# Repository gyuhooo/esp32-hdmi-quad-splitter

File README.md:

# esp32-hdmi-quad-splitter

Full HD のテスト映像を **1 台のデバイス内で生成し、HDMI 4 本に出力する**装置の設計。

> リポジトリ名は初期案(ESP32 + 分配器)に由来します。現在の方針は **FPGA によるテストパターン発生器**です。
> mp4 の再生は行わず、カラーバー・フレームカウンタ・タイムコードをロジックで生成して 4 本を独立したタイミングで出します。

## 現在の方針: FPGA 4 出力テストパターン発生器

| 項目 | 内容 |
|---|---|
| FPGA | Xilinx Artix-7 XC7A35T 以上(無償 Vivado、MMCM ×4 で 6 種のピクセルクロックを 1 ppm 以内で生成) |
| HDMI 送信 | ADI ADV7513 ×4(24bit RGB パラレル入力 → HDMI 1.4、1080p60 対応、資料公開) |
| 出力 | 1080p / 720p / 480p × 29.97p / 59.94p / 30p / 60p を出力ごとに独立して設定 |
| 画面 | 75% カラーバー、動くボックス(コマ落ち検出)、グレースケール、外枠、ラベル、6 桁フレームカウンタ、タイムコード |
| 状態 | HDL 一式と iverilog シミュレーション済み。基板は 2 枚(FPGA メイン基板 115 × 72 mm + HDMI キャリア基板 115 × 38 mm、どちらも 6 層)で、回路図・レイアウト・ガーバーまで生成済み。実機は未評価 |

```
100 MHz --> [Artix-7: MMCM x4 -> timing -> pattern] --24bit RGB--> [ADV7513] --> HDMI OUT1
                                   |                              [ADV7513] --> HDMI OUT2
                                   |                              [ADV7513] --> HDMI OUT3
                                   +---------- I2C 初期化 ------->[ADV7513] --> HDMI OUT4
```

シミュレーション結果(1080p 59.94 / 480p 59.94):

詳細は [docs/fpga-pattern-generator.md](docs/fpga-pattern-generator.md)。

### 試す

```
cd sim && make MODE=1 FRAME=2     # iverilog で 1080p59.94 の 1 フレームを frame.ppm に保存
```

### 基板(hardware/)

2 枚構成。下が FPGA メイン基板(XC7A35T-1FTG256C、QSPI フラッシュ、JTAG、100 MHz、USB-C 5 V → 1.0 / 1.8 / 3.3 V)、
上が HDMI キャリア基板(ADV7513 ×4、TPD12S016 ×4、HDMI ×4、USB-C 5 V 入力、3.3 V バック、1.8 V LDO ×4)で、2×40 ソケット 2 個で重ねる。
[hardware/README.md](hardware/README.md)(キャリア基板)と [hardware/fpga_main/README.md](hardware/fpga_main/README.md)(メイン基板)に構成・検証状況・発注前チェックリストがある。
FPGA のピン割り当ては生成済みで、`constraints/board.xdc` がそのまま Vivado で使える。

FPGA メイン基板(6 層、115 × 72 mm、表面。上部 y < 38 mm にキャリア基板が重なる):

簡易 3D(`hardware/fpga_main/3d/viewer.html`):

基板の簡易 3D モデル(`hardware/quad_hdmi_tx/3d/`、three.js ビューア付き):

基板レイアウト(6 層、115 × 38 mm、表面):

### ディレクトリ

| パス | 内容 |
|---|---|
| hardware/ | KiCad 7 プロジェクト ×2(FPGA メイン基板、HDMI キャリア基板)、BOM、ピン割り当て表、生成スクリプト |
| hdl/ | Verilog ソース(タイミング、パターン、文字重畳、MMCM、ADV7513 初期化、トップ) |
| sim/ | iverilog テストベンチと Makefile |
| constraints/ | Vivado 制約ファイルの例 |
| tools/make-font.py | フォント ROM 生成 |
| docs/ | 設計文書 |

## 検討経緯

| 案 | 判定 | 理由 |
|---|---|---|
| ESP32 + LT86104SX 分配器 | 不採用 | ESP32 は映像を生成できない。分配器は同一映像しか出せない |
| RK3588 で mp4 を再生し 4 CRTC へ | 代替案 | 自己完結するが、Linux と SoM が要り、出力ごとの独立タイミングは難しい。[docs/self-contained.md](docs/self-contained.md) |
| Ambarella A7 | 不採用 | HDMI 1 本、SDK は NDA |
| **FPGA パターン発生器** | **採用** | テストパターンで十分。出力ごとに独立したクロックを持て、BOM が小さい |

---

## 初期案(参考): ESP32 + LT86104SX 分配器

以下は「外部 HDMI ソース + 分配器を ESP32 で制御する」初期案の記録です。同一映像の 4 分配だけが目的ならこの構成でも成立します。

### 結論: 実現可能(ただし ESP32 は「制御担当」)

| 役割 | 担当 | 備考 |
|---|---|---|
| Full HD 映像の生成 | PC(ffmpeg) | [docs/video-source.md](docs/video-source.md) |
| Full HD 映像の再生(HDMI ソース) | **Raspberry Pi 4/5 など**(mpv) | ESP32 単体では不可 |
| 1→4 分配、HDCP リピータ、EDID 処理 | LT86104SX | 1080p60 まで、3.4 Gbps/ch |
| IC の初期化・EDID 管理・入力監視・出力 ON/OFF | ESP32(I2C マスタ) | Wi-Fi 経由でリモート制御も可 |

- LT86104SX は入力 HDMI 信号をそのまま 4 系統へ複製する IC で、映像の生成や解像度変換は行いません。
- ESP32(無印 / S3 / C3)には TMDS 出力が無く、1080p60(約 4.5 Gbps)の映像を生成する帯域も持たないため、**映像ソースにはなれません**。
- したがって「ESP32 + LT86104SX」で成立するのは **`HDMI ソース → LT86104SX → HDMI×4` を ESP32 が I2C で制御する構成** です。同じ映像を 4 台のモニタに出す用途なら、これで十分です。

### 4 本が「別々の映像」である必要がある場合

スプリッタでは実現できません。RK3588(4 画面同時出力)や 4 出力 GPU(ASUS GT710-4H など)を使ってください。

### ESP32-P4 を映像ソースにできるか

ESP32-P4 は MIPI-DSI(2 レーン)と H.264 デコーダを持つため、`ESP32-P4 → LT9611 / LT8912B (DSI→HDMI) → LT86104SX` で **1080p30 程度のテストパターン/静止画** を出すことは原理的に可能です。ただし 1080p60(RGB888 で約 3.56 Gbps)は DSI 帯域を超えるため、59.94p / 60p のテストは不可です。本リポジトリでは扱いません。

### ブロック図

```
[PC: ffmpeg で生成] --master.mp4--> [Raspberry Pi: mpv でループ再生]
                                              | HDMI 1080p
                                        [LT86104SX] --HDMI--> OUT1
                                           |   |------HDMI--> OUT2
                                           |   |------HDMI--> OUT3
                                           |   '------HDMI--> OUT4
                                           | I2C (SDA/SCL), RESET, INT
                                        [ESP32] <--Wi-Fi--> OBS-RemoteControl 等
```

### 最小構成の BOM

### 映像ソース

| 部品 | 数 | 備考 |
|---|---|---|
| Raspberry Pi 4(2 GB 以上)または Pi 5 | 1 | mpv でループ再生 |
| microSD 16 GB 以上 | 1 | Raspberry Pi OS Lite 64bit |
| micro HDMI → HDMI ケーブル | 1 | LT86104SX 入力へ |
| 5V 3A(Pi4)/ 5V 5A(Pi5)電源 | 1 | |
| 生成用 PC(ffmpeg) | 1 | 手元の PC で可 |

### スプリッタ + 制御

| 部品 | 数 | 備考 |
|---|---|---|
| LT86104SX(LQFP-128) | 1 | Lontium。データシート/レジスタ仕様は代理店経由(NDA)で入手 |
| ESP32 モジュール(ESP32-WROOM-32 / S3) | 1 | I2C マスタ、Wi-Fi |
| HDMI レセプタクル | 5 | 入力 1、出力 4 |
| 3.3V / コア用レギュレータ | 各 1 | 電圧は LT86104SX データシートで要確認 |
| ESD 保護ダイオード(TMDS 用) | 5 セット | 入出力各ポート |
| 水晶(周波数はデータシートで要確認) | 1 | |
| I2C プルアップ 4.7 kΩ | 2 | |
| 5V → HDMI +5V(各出力) | 4 | 出力側ホットプラグ用に 5V を給電 |

完成品の 1×4 スプリッタ基板(LT86104 搭載)を購入し、基板上の I2C を ESP32 に引き出す方法が最も安価で確実です。

### 使い方(映像の生成と再生)

```
# PC で生成 (ffmpeg 必須)
tools/generate-test-video.sh out/test-video 3

# Raspberry Pi に master.mp4 をコピーしてループ再生 (mpv 必須)
tools/play-loop.sh master.mp4
# セグメントごとに HDMI 出力モードを切替してテストする場合
tools/play-loop.sh --native segments
```

### 詳細

- [docs/self-contained.md](docs/self-contained.md): **現在の方針**。デバイス内で生成して 4 本出す構成
- [docs/video-source.md](docs/video-source.md): 映像の生成と再生機に必要なもの(初期案)
- [docs/feasibility.md](docs/feasibility.md): 可否判断の根拠、帯域計算
- [docs/hardware.md](docs/hardware.md): 配線、電源、注意点
- [docs/i2c-control.md](docs/i2c-control.md): ESP32 からの制御シーケンス
- [tools/](tools/): テスト映像の生成・再生スクリプト
- [firmware/](firmware/): ESP-IDF 用 I2C 制御の雛形

### 関連

- [OBS-RemoteControl](https://github.com/gyuhooo/OBS-RemoteControl)(テスト映像スクリプトの元)
- [LT86104SXE Product Brief (Lontium)](https://www.lontiumsemi.com/UploadFiles/2021-03/LT86104SXE_brief_R1.pdf)

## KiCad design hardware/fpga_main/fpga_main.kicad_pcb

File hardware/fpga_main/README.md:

# FPGA メイン基板 (XC7A35T-1FTG256C)

キャリア基板 `quad_hdmi_tx`(rev B、ADV7513 ×4 → HDMI ×4)をソケットで上に重ねて使う、FPGA 搭載のメイン基板。
2 枚構成の下側で、電源・コンフィグ用フラッシュ・JTAG・100 MHz 発振器・ユーザ I/O を持つ。
キャリア基板の裏面ヘッダ J7/J8(2×40 SMD)に、この基板の表面ソケット J1/J2(2×40 THT)が嵌合する。

| ファイル | 内容 |
|---|---|
| fpga_main.kicad_pro / *.kicad_sch | KiCad 7 プロジェクト(ルート + 電源 + FPGA I/O + FPGA コンフィグ/電源ピン + キャリアソケット + ユーザ I/O) |
| fpga_main.pdf | 回路図 PDF(6 ページ) |
| netlist.net | kicad-cli で書き出したネットリスト |
| bom.csv, bom_grouped.csv | 部品表(リファレンス別 / 集計、MPN 付き) |
| fpga_pinmap.csv | 全 256 ボールの表: ピン名、バンク、ネット、キャリアのヘッダピン、方向、エスケープ層。`gen/gen_xdc.py` が `constraints/board.xdc` を作る元 |
| roles.json | 自動採番された R/C の役割 → リファレンス(レイアウト生成が配置に使う) |
| fpga_main.kicad_pcb | 基板レイアウト rev A(6 層、115 × 72 mm)。`gen/gen_fpga_pcb.py` が配置・プレーン・BGA ファンアウトを生成し、FreeRouting で自動配線 |
| drc.rpt / drc_pre.rpt | DRC レポート(配線後 / 配線前) |
| fab/ | ガーバー、ドリル、CPL、各層の PDF(`gen/export_fab.sh fpga_main`) |
| 3d/ | STEP(基板のみ)、簡易 3D モデル(OBJ + テクスチャ)、three.js ビューア |

## 回路構成

```
USB-C 5V ─ F1(PTC 2A) ─ +5V ─┬─ U3 AP63200 ─ +1V0 (VCCINT/VCCBRAM)   EN: 即時
                             ├─ U4 AP63200 ─ +1V8 (VCCAUX)           EN: 100k + 1uF  (約 30 ms 遅れ)
                             └─ U5 AP63203 ─ +3V3 (VCCO 全バンク, フラッシュ, 発振器, LED) EN: 100k + 2.2uF (約 60 ms 遅れ)
U1 XC7A35T-1FTG256C ─┬─ U2 W25Q32JV (QSPI x4、Master SPI、M[2:0]=001)
                     ├─ J3 JTAG 2x7 2.0 mm (Xilinx 14 ピン) / J4 JTAG 1x6 (Digilent HS2 配列) ─ 並列
                     ├─ X1 100 MHz → D4 (IO_L12P_T1_MRCC_35)
                     ├─ SW1 PROG(PROGRAM_B)、SW2 RST(RST_N)、SW3 DIP ×4、D1-D7 LED(PWR/DONE/INIT/USER0-3)、J5 PMOD(8 I/O)
                     └─ J1/J2 2x40 ソケット ─ キャリア基板 J7/J8 (124 信号 + GND 34 + FPGA_5V 2)
```

### FPGA まわり

| 要素 | 内容 | 根拠・備考 |
|---|---|---|
| XC7A35T-1FTG256C | 170 I/O(バンク 14/15/34/35、各 50/50/20/50)、VCCO は全バンク 3.3 V | FTG256 は 1.0 mm ピッチの 16×16 BGA。6 層で全ピンを引き出せる(下記エスケープ) |
| VCCINT / VCCBRAM = 1.0 V | 同じレール(-1 スピードグレードでは VCCBRAM = VCCINT = 1.0 V が可) | DS181 |
| VCCAUX / VCCADC / VCCBATT = 1.8 V | XADC は未使用: VREFP/VREFN/VP/VN/GNDADC → GND、DXP/DXN 開放 | UG480 / UG475 |
| コンフィグ | Master SPI x4。M0 = 4.7k プルアップ、M1/M2 = GND、CFGBVS = VCCO_0 = 3.3 V | UG470 |
| PROGRAM_B | 4.7k プルアップ + タクトスイッチ SW1 | |
| INIT_B | 4.7k プルアップ + 赤 LED(Low のとき点灯 = 未コンフィグ / CRC エラー) | |
| DONE | 330 Ω プルアップ + 緑 LED(1k) | UG470 の推奨 330 Ω。LED 点灯時も DONE は約 3.0 V で High |
| フラッシュ | W25Q32JVSSIQ(32 Mbit、ビットストリーム 17.5 Mbit) CS/WP/HOLD 4.7k プルアップ、CCLK は E8、D0-D3 は J13/J14/K15/K16、FCS_B は L12 | バンク 14 のコンフィグ兼用ピン |
| JTAG | TMS/TDI 4.7k プルアップ(TCK/TDO は内蔵プルアップのみ) | |
| 発振器 | ASEM1-100.000MHZ-LC-T(3.2 × 2.5 mm、3.3 V、±50 ppm)、MRCC ピン D4 へ | hdl/top.v の clk100 |
| デカップリング | +1V0: 100 µF + 4.7 µF ×2 + 0.47 µF ×4、+1V8: 47 µF + 4.7 µF + 0.47 µF ×2、+3V3: 47 µF + 4.7 µF ×4(バンクごと) + 0.47 µF ×9 | UG483 の FTG256 推奨数量以上。0.47 µF は BGA 直下の十字通路と周囲(裏面) |

### キャリア基板とのインタフェース

- J1(= キャリア J7)、J2(= キャリア J8): 2×40 メス(Sullins PPTC402LFBN-RC、高さ 8.5 mm)。ピン n はキャリアの同じ番号のピンと一致する。
- 位置はキャリアの J7/J8 のピン位置の鏡像: J1 の奇数ピン y = 16.93 / 偶数 19.47 mm、J2 の奇数 32.33 / 偶数 34.87 mm、列 k の x = 2.07 + 2.54 (k−1) mm(基板左上が原点、両基板とも同じ原点・同じ向き)。
- キャリアの SMD ヘッダの本体(2.54 mm)+ ソケット(8.5 mm)で基板間は約 11 mm。取付穴 H1-H4 はキャリアと同じ位置(26.2, 3)(51.6, 3)(77, 3)(112, 35)で、M3 × 11 mm のスペーサで固定する。
- y < 38 mm はキャリアの真下で、ソケット以外の部品は置いていない(キャリア裏面の LDO・コンデンサと干渉しない)。
- FPGA_5V(J2 の 39/40 ピン)は JP1 で +5V に繋げる。既定は開放(両基板とも自分の USB-C から給電)。両基板の JP1 を閉じると片方の USB-C で両方を動かせる(合計 2 A まで)。
- I2C のプルアップ(4.7 kΩ)はキャリア側にある。

### ユーザ I/O

| 部品 | ネット | FPGA ボール | 用途 |
|---|---|---|---|
| D4-D7(緑) | LED0-3 | R10, R11, T12, R12 | hdl/top.v の `led[3:0]`(各チャネルの初期化完了) |
| SW2 | RST_N(10k プルアップ、0.1 µF) | T3 | `rst_n` |
| SW3 DIP ×4 | SW0-3(閉で Low、内蔵プルアップを XDC で有効化) | T13, R13, T14, T15 | 予備(ビデオモード切替用) |
| J5 PMOD 2×6 | PMOD_1-4 / 7-10、GND、3.3 V | E5, E6, F5, G5, H5, J5, K5, L5(バンク 35) | 予備 I/O(Digilent Pmod 配列) |
| D1-D3 | 3.3 V / DONE / INIT_B | — | 電源 / コンフィグ完了 / 未コンフィグ |

## ピン割り当て

`gen/fpga_common.py` が決める(回路図とレイアウトの両方が同じモジュールを使うので食い違わない)。

1. **BGA エスケープ計画**: ボールのリングごとに引き出し方を固定する。リング 1(最外周)は表面パッドから直接、リング 2 は表面でリング 1 のパッドの隙間へ、
   リング 3-4 は外向き対角のセルに dog-bone ビアを打ち In2(SIG1)で整数格子線に沿って外へ、リング 5 以降の信号(JTAG、CCLK、DONE、INIT_B、PROGRAM_B、M0、PMOD)は In3(SIG2)。
   整数格子線は層ごとに 1 本の配線が占有し、各ビアは隣接 4 格子点のどれかから最寄りの辺へ向かう(占有点が重ならないよう貪欲に割り当て)。GND/電源ボールは dog-bone ビアでプレーンへ。
2. **ヘッダ信号の割り当て**: 124 本のヘッダ信号を x 順(列 k、列内は J1 奇 / J2 奇 / J2 偶 / J1 偶)に並べ、BGA の出口を周回順(左下 → 左辺 → 上辺 → 右辺 → 右下)に並べたものへ単調に対応させる。
   124 個の連続した出口の窓のうち、ヘッダピンまでの距離の総和が最小のものを選ぶ。交差が出ないので、ソケットまでの配線が素直になる。
3. 用途が決まっているボール(フラッシュ、クロック、LED、スイッチ、PMOD)は先に確保する。

結果(`fpga_pinmap.csv`): OUT1 = バンク 34/35(左辺・下辺左)、OUT2 = バンク 35(上辺左・左辺)、OUT3 = バンク 15(上辺右)、OUT4 = バンク 14/15(右辺・下辺右)。
I2C_A は H4/H2(バンク 35)、I2C_B は E15/E16(バンク 15)。未使用 I/O はリング 1-4 に 10 本、リング 5-6 に 11 本(開放)。

Vivado 用の制約は `python3 hardware/gen/gen_xdc.py > constraints/board.xdc`(hdl/top.v のポート名、`SLEW FAST`、CFGBVS/CONFIG_VOLTAGE、QSPI x4、非同期クロックグループ)。

## 基板レイアウト

### 配置(rev A: 115 × 72 mm)

```
y=0  ┌──────────────────────────────────────────────────────────────────────┐
     │  (キャリア基板の真下: H1 H2 H4 取付穴、部品なし)                       │
 17  │  J1 ████████████████████████████████████████████ (2x40 ソケット)       │
 33  │  J2 ████████████████████████████████████████████                     H3 │
 38  ├─ キャリア基板の下端 ─────────────────────────────────────────────────┤
     │ PMOD                      ┌─────────┐      U2 flash  C(3V3 47u) USB-C │
 55  │ J5   X1 100MHz  caps      │ U1 BGA  │ caps  R pull-up  U3   U4   U5   │
     │                           │ 16x16   │      1V0  1V8  3V3 bucks         │
 69  │ H5 J3 JTAG2mm  J4 JTAG1x6  PROG RST  DIP  LEDs x7           H6        │
 72  └──────────────────────────────────────────────────────────────────────┘
```

- FPGA は露出部の中央 (51.6, 55):ヘッダ中心 x と同じで、左右の信号本数が揃う。ソケット J2 の下端(y 35.7)から BGA のエスケープ終端(y 46)まで 10 mm の帯で 124 本をファンアウトする。
- J1 の信号は J2 のスルーホール列を内層で抜ける。ソケットのパッドはライブラリの 1.7 mm から 1.5 mm(穴 1.0 mm、アニュラ 0.25 mm)に縮めて列の隙間を 1.04 mm にし、隙間 1 つに 0.15 mm 配線 2 本(4 層で最大 8 本)が通る。
- フラッシュ U2 は BGA 右(バンク 14 のコンフィグピンは右辺の行 8-10 から出る)、発振器 X1 は左(D4 は In2 で左辺へ)。
- 電源は右下: USB-C は右辺、バック 3 個を横並び(1.0 V が FPGA に最も近い)。+5V は In4 の櫛形プレーン(バー + 各バックの IN 側の歯)。
- +1V0 は In4 の島(BGA 中央、VCCINT/VCCBRAM のビアを含み VCCO_0 のビアは避ける)→ 列 7.5 の通路(ビアのない中央の十字)→ 下の帯(y 65-67.6)→ U3 出力。
- +1V8 は裏面ベタ: BGA 中央右(VCCAUX ×4、VCCADC、VCCBATT)→ 行 7.5 の通路 → U4 出力への帯。
- デカップリングは裏面。0.47 µF は BGA 直下の十字通路(列 7.5 に +1V0 ×3、行 7.5 に +1V0 ×1 と +1V8 ×2、ビアはセル中心 = 半整数格子)と BGA の左右(VCCO)。バルクは下の帯と各バックの脇。

### 層構成(6 層、1.6 mm)

| 層 | 用途 |
|---|---|
| F.Cu | 部品、BGA リング 1-2 のエスケープ、配線後に GND ベタ |
| In1.Cu | GND プレーン |
| In2.Cu (SIG1) | BGA リング 3-4 のエスケープ(整数格子線)、信号 |
| In3.Cu (SIG2) | 深いリングの信号のエスケープ、信号 |
| In4.Cu (PWR) | +3V3 プレーン + +1V0 の島/腕/帯 + +5V の櫛 |
| B.Cu | デカップリング、+1V8 ベタ(BGA 中央右)、信号、配線後に GND ベタ |

### ルール

配線 0.15 mm / クリアランス 0.15 mm(BGA の 1.0 mm ピッチで、ビア 0.5 mm の隙間 0.5 mm に 0.15 mm 配線を 1 本通すため)、ビア 0.5 / 0.3 mm(アニュラ 0.1 mm)、
穴-銅 0.18 mm、銅-外形 0.3 mm。電源ネットクラス(+5V/+3V3/+1V0/+1V8/VBUS/FPGA_5V/SW ノード)は 0.4 mm 幅、ビア 0.6 mm。
dog-bone ビアは隣のボールパッド(0.4 mm)から 0.26 mm、整数格子線の配線はビアパッドから 0.175 mm 離れる。

### 生成と配線のパイプライン

```sh
cd hardware/gen
./build_fpga_main.sh                      # 回路図 → netlist.net → 基板 (配置 + BGA ファンアウト + 電源ビア) → ゾーン塗り + drc_pre.rpt
PCB_PROJECT=fpga_main python3 route_pcb.py export        # fpga_main.dsn
(cd ../fpga_main && xvfb-run -a -s "-screen 0 1280x1024x24" java -jar freerouting-1.9.0.jar -de fpga_main.dsn -do fpga_main.ses -mp 24 -oit 1.0)
PCB_PROJECT=fpga_main python3 route_pcb.py import        # SES 取り込み、未接続の島の接続、外層 GND ベタ、drc.rpt
PCB_PROJECT=fpga_main python3 layout_report.py
./export_fab.sh fpga_main                 # fab/
PY=../../../scratch/venv/bin/python ./make_3d.sh fpga_main   # 3d/: STEP、簡易 OBJ、テクスチャ、viewer.html (PY は Pillow/numpy 入りの python)
PCB_PROJECT=fpga_main ../../scratch/venv/bin/python render_images.py   # docs/images/fpga-main-*.png
python3 gen_xdc.py > ../../constraints/board.xdc
python3 check_fpga_netlist.py ../fpga_main/netlist.net && python3 check_stack.py
```

## 検証状況

- 回路図: `gen/check_fpga_netlist.py` でネットリストを検査(ヘッダ信号 124 本が J1/J2 と U1 の 2 ノード、全 256 ボールが接続または NC、電源ネットに信号ボールが混ざっていない、孤立ネットなし)。ERC は未実施(kicad-cli 7 に無い)。
- 2 枚構成: `gen/check_stack.py` でキャリアのヘッダピンとソケットピンの位置(誤差 0.000 mm)、ピンごとのネット、取付穴 H1-H4 の一致を確認。
- レイアウト: 配線前 DRC はクリアランス / 穴 / コートヤード違反 0(BGA ファンアウト 149 ビア + 112 エスケープ、電源ファンアウトビア 125)。配線後の結果は下記(未接続 0、違反 0)。
- 実機・Vivado での実装は未実施。

### レイアウトの結果

| 項目 | 値 |
|---|---|
| 配線 / ビア | 2155 本 / 405 個(スクリプトの固定配線 522 本・ビア 285 個を含む。ビアは 0.5/0.3 mm ×279、0.6/0.3 mm ×126) |
| DRC(pcbnew API) | 未接続 0、クリアランス / 穴 / 外形 / コートヤード / シルク違反 0。残り 109 件は `lib_footprint_issues`(ライブラリ名なしで読み込んだフットプリントの照合情報)のみ |
| ヘッダ信号 124 本の配線長 | OUT1 33〜83 mm(平均 56)、OUT2 14〜49(30)、OUT3 13〜46(28)、OUT4 31〜89(55)。FR4 の 90 mm は約 0.6 ns で、148.5 MHz SDR の余裕(数 ns)に収まる |
| 層別の配線長 | F 1077 mm、In2 (SIG1) 4072、In3 (SIG2) 1039、B 412 |
| 自動配線 | FreeRouting 1.9.0、40 パス、約 8 分(ルータにはビア禁止領域: BGA 直下・+1V0 の腕・裏面の +1V8 帯・外形から 0.45 mm を渡す)。INIT_B の LED 側 1 区間だけ `route_pcb.py` の MANUAL で手配線 |

| 層 | 画像 |
|---|---|
| 表面 (F.Cu) |  |
| 裏面 (B.Cu、ミラー表示) |  |
| 内層 1 (GND) |  |
| 内層 2 (SIG1: BGA リング 3-4 のエスケープ) |  |
| 内層 3 (SIG2) |  |
| 内層 4 (PWR: +3V3 / +1V0 島 / +5V 櫛) |  |

### 3D モデル

`3d/`: STEP(基板のみ)、簡易 OBJ(部品は寸法表の直方体)、three.js ビューア `3d/viewer.html`(ブラウザで開く。ドラッグで回転)。
部品の外形は近似なので、正確な 3D が要るときは KiCad の 3D ライブラリを入れて `kicad-cli pcb export step` を再実行する。

| 斜め | 表 | 裏 |
|---|---|---|
|  |  |  |

## 発注前チェックリスト

- [ ] ソケット J1/J2 の高さ(8.5 mm)とキャリア側ヘッダの嵌合長(Samtec TSM の 0.230" ピン)を実物で確認。別の高さのソケットならスペーサ長を合わせる。
- [ ] UG483 の表(FTG256 の必要コンデンサ数)と `fpga_cfg.kicad_sch` のデカップリング数量を照合(ここでは余裕を持って多めにしている)。
- [ ] AP63200 の FB 分圧(1.0 V: 10k / 40.2k、1.8 V: 24.9k / 20k)と EN の RC 遅延(データシートの EN しきい値 1.2 V 前後)を確認。
- [ ] JTAG ヘッダの配列(J3: Xilinx 14 ピン 2 mm、J4: Digilent HS2 6 ピン)を使うケーブルと照合。
- [ ] DIP スイッチ(Copal CHS-04B)、タクトスイッチ(C&K KMR2)、発振器(Abracon ASEM1)の入手性。代替品はフットプリントを合わせる。
- [ ] フラッシュ W25Q32JV: Vivado のメモリ構成ファイルは `w25q32jv-spi-x1_x2_x4`。
- [ ] 1.0 mm ピッチ BGA の 0.15 / 0.15 mm ルール、ビア 0.3 / 0.5 mm(アニュラ 0.1 mm)が製造業者の 6 層仕様に収まるか。JLCPCB の 6 層は配線/間隔 0.09 mm、ビア穴 0.2 mm(径 0.35 mm 程度)以上、PTH のアニュラ 0.13 mm なので余裕があるが、注文時の仕様ページで再確認する。
- [ ] BGA 直下の In1/In4 プレーンはビアの間の 0.2 mm 幅のメッシュになる(1.0 mm ピッチ、ビア 0.5 mm + クリアランス 0.15 mm)。通常の設計と同じだが、ガーバーで確認。
- [ ] 外層 GND ベタは BGA 直下にも入る(パッド間 0.3 mm)。不要なら `route_pcb.py` の finish 段で BGA 領域を除外する。

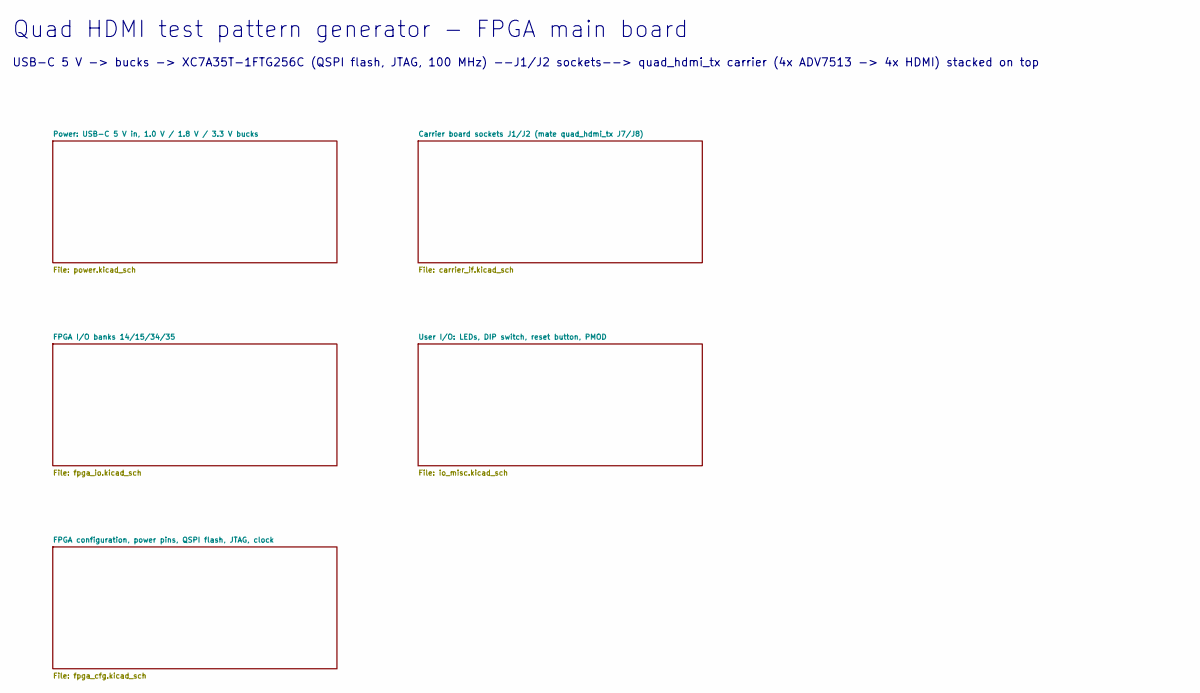
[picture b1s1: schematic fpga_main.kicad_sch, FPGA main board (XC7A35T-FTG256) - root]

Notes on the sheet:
Quad HDMI test pattern generator - FPGA main board
USB-C 5 V -> bucks -> XC7A35T-1FTG256C (QSPI flash, JTAG, 100 MHz) --J1/J2 sockets--> quad_hdmi_tx carrier (4x ADV7513 -> 4x HDMI) stacked on top

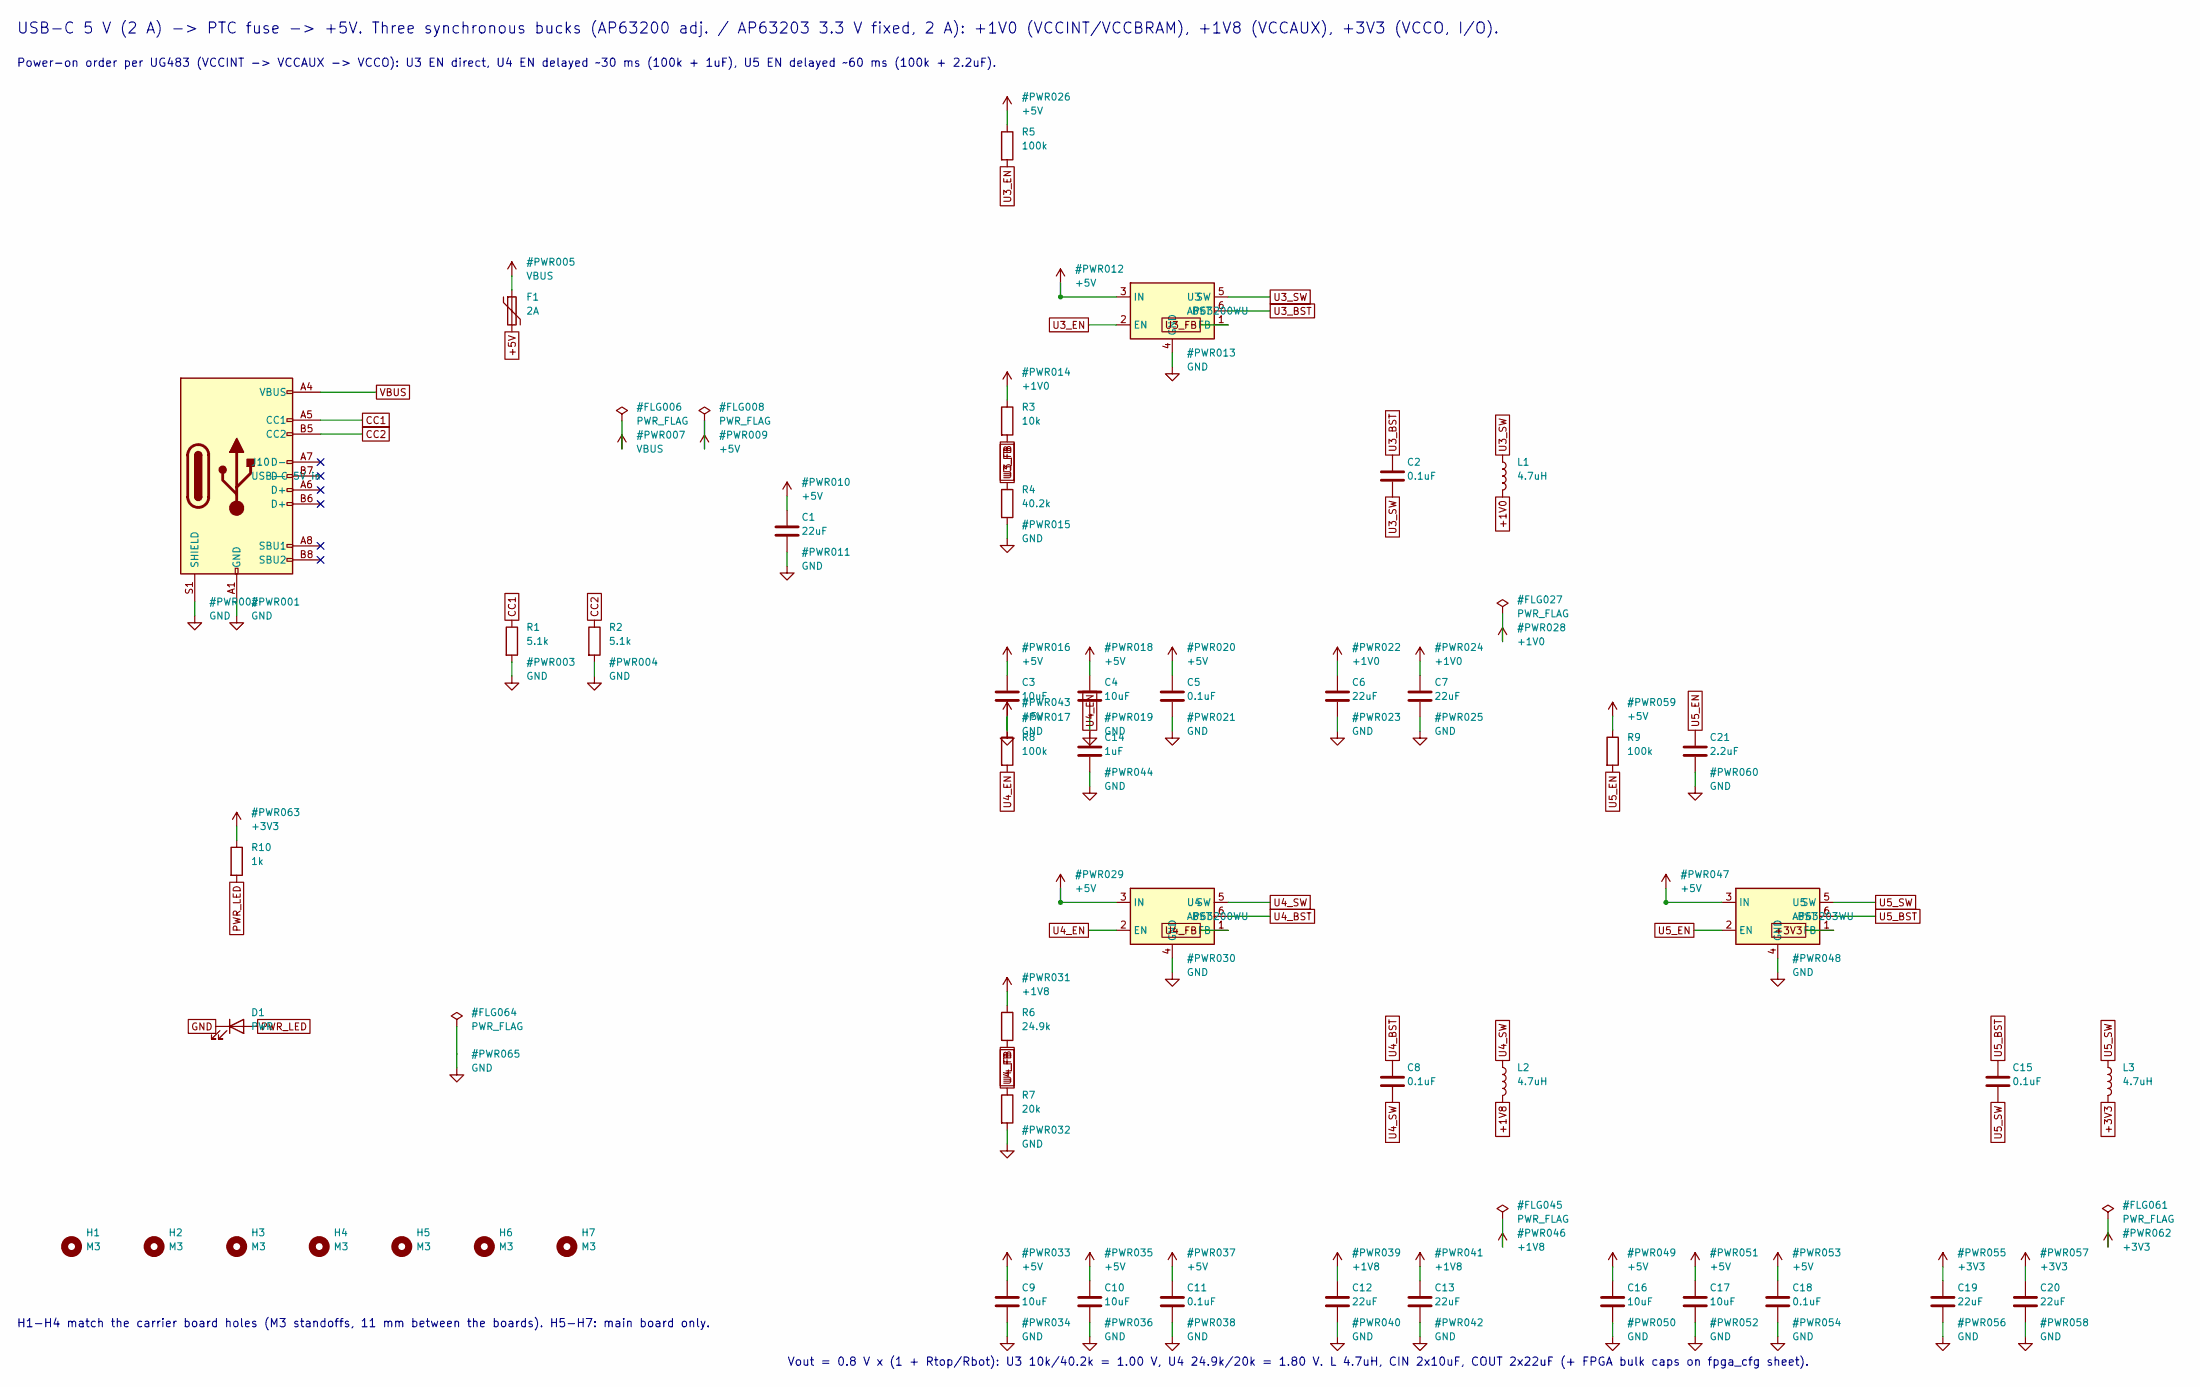
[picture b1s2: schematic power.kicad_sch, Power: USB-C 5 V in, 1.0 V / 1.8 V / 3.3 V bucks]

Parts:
C1, C6, C7, C12, C13, C19, C20: 22uF; C_0805_2012Metric; MPN GRM21BR60J226ME39L
C2, C5, C8, C11, C15, C18: 0.1uF; C_0402_1005Metric; MPN GRM155R71C104KA88D
C3, C4, C9, C10, C16, C17: 10uF; C_0805_2012Metric; MPN GRM21BR61A106KE19L
C14: 1uF; C_0603_1608Metric; MPN GRM188R61A105KA61D
C21: 2.2uF; C_0603_1608Metric; MPN GRM188R61A225KE34D
D1: PWR; LED_0603_1608Metric; MPN LTST-C193KGKT-5A
F1: 2A; Fuse_1206_3216Metric; MPN 1206L200/12SLYR
H1, H2, H3, H4, H5, H6, H7: M3; MountingHole_3.2mm_M3
J10: USB-C 5V in; USB_C_Receptacle_GCT_USB4105-xx-A_16P_TopMnt_Horizontal; MPN USB4105-GF-A
L1, L2, L3: 4.7uH; L_Taiyo-Yuden_NR-40xx; MPN NR4018T4R7M
R1, R2: 5.1k; R_0402_1005Metric; MPN RC0402FR-075K1L
R3: 10k; R_0402_1005Metric; MPN RC0402FR-0710KL
R4: 40.2k; R_0402_1005Metric; MPN RC0402FR-0740K2L
R5, R8, R9: 100k; R_0402_1005Metric; MPN RC0402FR-07100KL
R6: 24.9k; R_0402_1005Metric; MPN RC0402FR-0724K9L
R7: 20k; R_0402_1005Metric; MPN RC0402FR-0720KL
R10: 1k; R_0402_1005Metric; MPN RC0402FR-071KL
U3, U4: AP63200WU; TSOT-23-6; MPN AP63200WU-7
U5: AP63203WU; TSOT-23-6; MPN AP63203WU-7

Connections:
+1V0: C6.1, C7.1, L1.2, R3.1; also elsewhere on the board
+1V8: C12.1, C13.1, L2.2, R6.1; also elsewhere on the board
+3V3: C19.1, C20.1, L3.2, R10.1, U5.1 (FB); also elsewhere on the board
+5V: C1.1, C3.1, C4.1, C5.1, C9.1, C10.1, C11.1, C16.1, C17.1, C18.1, F1.2, R5.1, R8.1, R9.1, U3.3 (IN), U4.3 (IN), U5.3 (IN); also elsewhere on the board
CC1: J10.A5 (CC1), R1.1
CC2: J10.B5 (CC2), R2.1
PWR_LED: D1.2 (A), R10.2
U3_BST: C2.1, U3.6 (BST)
U3_EN: R5.2, U3.2 (EN)
U3_FB: R3.2, R4.1, U3.1 (FB)
U3_SW: C2.2, L1.1, U3.5 (SW)
U4_BST: C8.1, U4.6 (BST)
U4_FB: R6.2, R7.1, U4.1 (FB)
U4_SW: C8.2, L2.1, U4.5 (SW)
U5_BST: C15.1, U5.6 (BST)
U5_EN: C21.1, R9.2, U5.2 (EN)
U5_SW: C15.2, L3.1, U5.5 (SW)
VBUS: F1.1, J10.A4 (VBUS), J10.A9 (VBUS), J10.B4 (VBUS), J10.B9 (VBUS)

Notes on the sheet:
USB-C 5 V (2 A) -> PTC fuse -> +5V. Three synchronous bucks (AP63200 adj. / AP63203 3.3 V fixed, 2 A): +1V0 (VCCINT/VCCBRAM), +1V8 (VCCAUX), +3V3 (VCCO, I/O).
Power-on order per UG483 (VCCINT -> VCCAUX -> VCCO): U3 EN direct, U4 EN delayed ~30 ms (100k + 1uF), U5 EN delayed ~60 ms (100k + 2.2uF).
Vout = 0.8 V x (1 + Rtop/Rbot): U3 10k/40.2k = 1.00 V, U4 24.9k/20k = 1.80 V. L 4.7uH, CIN 2x10uF, COUT 2x22uF (+ FPGA bulk caps on fpga_cfg sheet).
H1-H4 match the carrier board holes (M3 standoffs, 11 mm between the boards). H5-H7: main board only.

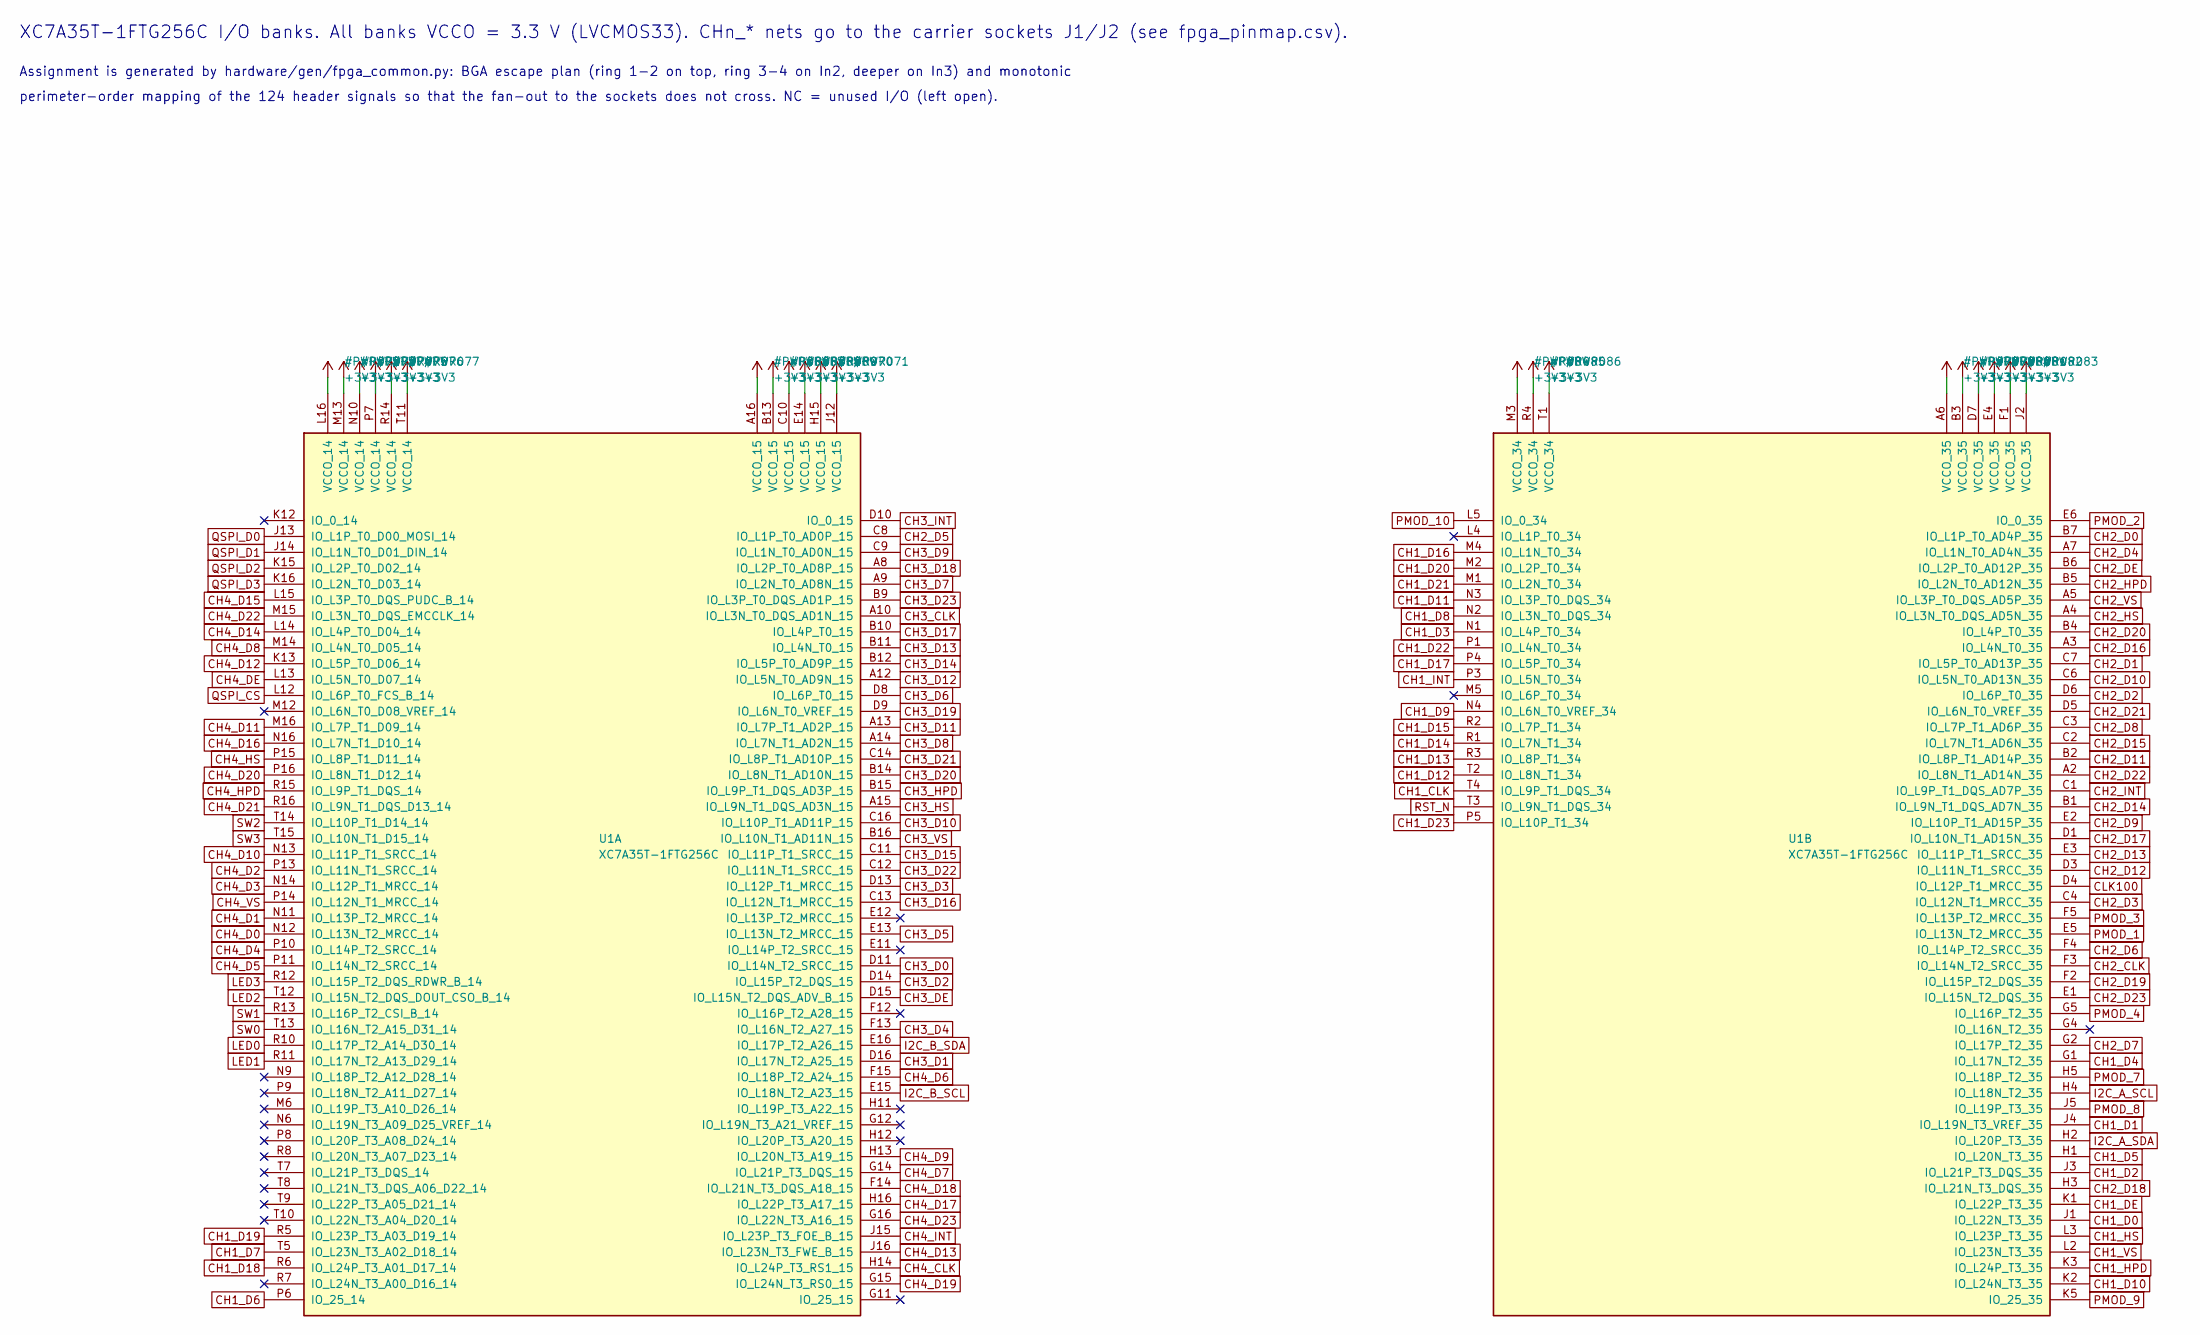
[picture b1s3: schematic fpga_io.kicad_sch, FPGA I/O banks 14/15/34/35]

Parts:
U1: XC7A35T-1FTG256C; Xilinx_FTG256; MPN XC7A35T-1FTG256C

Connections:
+3V3: U1.A6 (VCCO_35), U1.A16 (VCCO_15), U1.B3 (VCCO_35), U1.B13 (VCCO_15), U1.C10 (VCCO_15), U1.D7 (VCCO_35), U1.E4 (VCCO_35), U1.E14 (VCCO_15), U1.F1 (VCCO_35), U1.H15 (VCCO_15), U1.J2 (VCCO_35), U1.J12 (VCCO_15), U1.L16 (VCCO_14), U1.M3 (VCCO_34), U1.M13 (VCCO_14), U1.N10 (VCCO_14), U1.P7 (VCCO_14), U1.R4 (VCCO_34), U1.R14 (VCCO_14), U1.T1 (VCCO_34), U1.T11 (VCCO_14); also elsewhere on the board
CH1_CLK: U1.T4 (IO_L9P_T1_DQS_34); also elsewhere on the board
CH1_D0: U1.J1 (IO_L22N_T3_35); also elsewhere on the board
CH1_D1: U1.J4 (IO_L19N_T3_VREF_35); also elsewhere on the board
CH1_D2: U1.J3 (IO_L21P_T3_DQS_35); also elsewhere on the board
CH1_D3: U1.N1 (IO_L4P_T0_34); also elsewhere on the board
CH1_D4: U1.G1 (IO_L17N_T2_35); also elsewhere on the board
CH1_D5: U1.H1 (IO_L20N_T3_35); also elsewhere on the board
CH1_D6: U1.P6 (IO_25_14); also elsewhere on the board
CH1_D7: U1.T5 (IO_L23N_T3_A02_D18_14); also elsewhere on the board
CH1_D8: U1.N2 (IO_L3N_T0_DQS_34); also elsewhere on the board
CH1_D9: U1.N4 (IO_L6N_T0_VREF_34); also elsewhere on the board
CH1_D10: U1.K2 (IO_L24N_T3_35); also elsewhere on the board
CH1_D11: U1.N3 (IO_L3P_T0_DQS_34); also elsewhere on the board
CH1_D12: U1.T2 (IO_L8N_T1_34); also elsewhere on the board
CH1_D13: U1.R3 (IO_L8P_T1_34); also elsewhere on the board
CH1_D14: U1.R1 (IO_L7N_T1_34); also elsewhere on the board
CH1_D15: U1.R2 (IO_L7P_T1_34); also elsewhere on the board
CH1_D16: U1.M4 (IO_L1N_T0_34); also elsewhere on the board
CH1_D17: U1.P4 (IO_L5P_T0_34); also elsewhere on the board
CH1_D18: U1.R6 (IO_L24P_T3_A01_D17_14); also elsewhere on the board
CH1_D19: U1.R5 (IO_L23P_T3_A03_D19_14); also elsewhere on the board
CH1_D20: U1.M2 (IO_L2P_T0_34); also elsewhere on the board
CH1_D21: U1.M1 (IO_L2N_T0_34); also elsewhere on the board
CH1_D22: U1.P1 (IO_L4N_T0_34); also elsewhere on the board
CH1_D23: U1.P5 (IO_L10P_T1_34); also elsewhere on the board
CH1_DE: U1.K1 (IO_L22P_T3_35); also elsewhere on the board
CH1_HPD: U1.K3 (IO_L24P_T3_35); also elsewhere on the board
CH1_HS: U1.L3 (IO_L23P_T3_35); also elsewhere on the board
CH1_INT: U1.P3 (IO_L5N_T0_34); also elsewhere on the board
CH1_VS: U1.L2 (IO_L23N_T3_35); also elsewhere on the board
CH2_CLK: U1.F3 (IO_L14N_T2_SRCC_35); also elsewhere on the board
CH2_D0: U1.B7 (IO_L1P_T0_AD4P_35); also elsewhere on the board
CH2_D1: U1.C7 (IO_L5P_T0_AD13P_35); also elsewhere on the board
CH2_D2: U1.D6 (IO_L6P_T0_35); also elsewhere on the board
CH2_D3: U1.C4 (IO_L12N_T1_MRCC_35); also elsewhere on the board
CH2_D4: U1.A7 (IO_L1N_T0_AD4N_35); also elsewhere on the board
CH2_D5: U1.C8 (IO_L1P_T0_AD0P_15); also elsewhere on the board
CH2_D6: U1.F4 (IO_L14P_T2_SRCC_35); also elsewhere on the board
CH2_D7: U1.G2 (IO_L17P_T2_35); also elsewhere on the board
CH2_D8: U1.C3 (IO_L7P_T1_AD6P_35); also elsewhere on the board
CH2_D9: U1.E2 (IO_L10P_T1_AD15P_35); also elsewhere on the board
CH2_D10: U1.C6 (IO_L5N_T0_AD13N_35); also elsewhere on the board
CH2_D11: U1.B2 (IO_L8P_T1_AD14P_35); also elsewhere on the board
CH2_D12: U1.D3 (IO_L11N_T1_SRCC_35); also elsewhere on the board
CH2_D13: U1.E3 (IO_L11P_T1_SRCC_35); also elsewhere on the board
CH2_D14: U1.B1 (IO_L9N_T1_DQS_AD7N_35); also elsewhere on the board
CH2_D15: U1.C2 (IO_L7N_T1_AD6N_35); also elsewhere on the board
CH2_D16: U1.A3 (IO_L4N_T0_35); also elsewhere on the board
CH2_D17: U1.D1 (IO_L10N_T1_AD15N_35); also elsewhere on the board
CH2_D18: U1.H3 (IO_L21N_T3_DQS_35); also elsewhere on the board
CH2_D19: U1.F2 (IO_L15P_T2_DQS_35); also elsewhere on the board
CH2_D20: U1.B4 (IO_L4P_T0_35); also elsewhere on the board
CH2_D21: U1.D5 (IO_L6N_T0_VREF_35); also elsewhere on the board
CH2_D22: U1.A2 (IO_L8N_T1_AD14N_35); also elsewhere on the board
CH2_D23: U1.E1 (IO_L15N_T2_DQS_35); also elsewhere on the board
CH2_DE: U1.B6 (IO_L2P_T0_AD12P_35); also elsewhere on the board
CH2_HPD: U1.B5 (IO_L2N_T0_AD12N_35); also elsewhere on the board
CH2_HS: U1.A4 (IO_L3N_T0_DQS_AD5N_35); also elsewhere on the board
CH2_INT: U1.C1 (IO_L9P_T1_DQS_AD7P_35); also elsewhere on the board
CH2_VS: U1.A5 (IO_L3P_T0_DQS_AD5P_35); also elsewhere on the board
CH3_CLK: U1.A10 (IO_L3N_T0_DQS_AD1N_15); also elsewhere on the board
CH3_D0: U1.D11 (IO_L14N_T2_SRCC_15); also elsewhere on the board
CH3_D1: U1.D16 (IO_L17N_T2_A25_15); also elsewhere on the board
CH3_D2: U1.D14 (IO_L15P_T2_DQS_15); also elsewhere on the board
CH3_D3: U1.D13 (IO_L12P_T1_MRCC_15); also elsewhere on the board
CH3_D4: U1.F13 (IO_L16N_T2_A27_15); also elsewhere on the board
CH3_D5: U1.E13 (IO_L13N_T2_MRCC_15); also elsewhere on the board
CH3_D6: U1.D8 (IO_L6P_T0_15); also elsewhere on the board
CH3_D7: U1.A9 (IO_L2N_T0_AD8N_15); also elsewhere on the board
CH3_D8: U1.A14 (IO_L7N_T1_AD2N_15); also elsewhere on the board
CH3_D9: U1.C9 (IO_L1N_T0_AD0N_15); also elsewhere on the board
CH3_D10: U1.C16 (IO_L10P_T1_AD11P_15); also elsewhere on the board
CH3_D11: U1.A13 (IO_L7P_T1_AD2P_15); also elsewhere on the board
CH3_D12: U1.A12 (IO_L5N_T0_AD9N_15); also elsewhere on the board
CH3_D13: U1.B11 (IO_L4N_T0_15); also elsewhere on the board
CH3_D14: U1.B12 (IO_L5P_T0_AD9P_15); also elsewhere on the board
CH3_D15: U1.C11 (IO_L11P_T1_SRCC_15); also elsewhere on the board
CH3_D16: U1.C13 (IO_L12N_T1_MRCC_15); also elsewhere on the board
CH3_D17: U1.B10 (IO_L4P_T0_15); also elsewhere on the board
CH3_D18: U1.A8 (IO_L2P_T0_AD8P_15); also elsewhere on the board
CH3_D19: U1.D9 (IO_L6N_T0_VREF_15); also elsewhere on the board
CH3_D20: U1.B14 (IO_L8N_T1_AD10N_15); also elsewhere on the board
CH3_D21: U1.C14 (IO_L8P_T1_AD10P_15); also elsewhere on the board
CH3_D22: U1.C12 (IO_L11N_T1_SRCC_15); also elsewhere on the board
CH3_D23: U1.B9 (IO_L3P_T0_DQS_AD1P_15); also elsewhere on the board
CH3_DE: U1.D15 (IO_L15N_T2_DQS_ADV_B_15); also elsewhere on the board
CH3_HPD: U1.B15 (IO_L9P_T1_DQS_AD3P_15); also elsewhere on the board
CH3_HS: U1.A15 (IO_L9N_T1_DQS_AD3N_15); also elsewhere on the board
CH3_INT: U1.D10 (IO_0_15); also elsewhere on the board
CH3_VS: U1.B16 (IO_L10N_T1_AD11N_15); also elsewhere on the board
CH4_CLK: U1.H14 (IO_L24P_T3_RS1_15); also elsewhere on the board
CH4_D0: U1.N12 (IO_L13N_T2_MRCC_14); also elsewhere on the board
CH4_D1: U1.N11 (IO_L13P_T2_MRCC_14); also elsewhere on the board
CH4_D2: U1.P13 (IO_L11N_T1_SRCC_14); also elsewhere on the board
CH4_D3: U1.N14 (IO_L12P_T1_MRCC_14); also elsewhere on the board
CH4_D4: U1.P10 (IO_L14P_T2_SRCC_14); also elsewhere on the board
CH4_D5: U1.P11 (IO_L14N_T2_SRCC_14); also elsewhere on the board
CH4_D6: U1.F15 (IO_L18P_T2_A24_15); also elsewhere on the board
CH4_D7: U1.G14 (IO_L21P_T3_DQS_15); also elsewhere on the board
CH4_D8: U1.M14 (IO_L4N_T0_D05_14); also elsewhere on the board
CH4_D9: U1.H13 (IO_L20N_T3_A19_15); also elsewhere on the board
CH4_D10: U1.N13 (IO_L11P_T1_SRCC_14); also elsewhere on the board
CH4_D11: U1.M16 (IO_L7P_T1_D09_14); also elsewhere on the board
CH4_D12: U1.K13 (IO_L5P_T0_D06_14); also elsewhere on the board
CH4_D13: U1.J16 (IO_L23N_T3_FWE_B_15); also elsewhere on the board
CH4_D14: U1.L14 (IO_L4P_T0_D04_14); also elsewhere on the board
CH4_D15: U1.L15 (IO_L3P_T0_DQS_PUDC_B_14); also elsewhere on the board
CH4_D16: U1.N16 (IO_L7N_T1_D10_14); also elsewhere on the board
CH4_D17: U1.H16 (IO_L22P_T3_A17_15); also elsewhere on the board
CH4_D18: U1.F14 (IO_L21N_T3_DQS_A18_15); also elsewhere on the board
CH4_D19: U1.G15 (IO_L24N_T3_RS0_15); also elsewhere on the board
CH4_D20: U1.P16 (IO_L8N_T1_D12_14); also elsewhere on the board
CH4_D21: U1.R16 (IO_L9N_T1_DQS_D13_14); also elsewhere on the board
CH4_D22: U1.M15 (IO_L3N_T0_DQS_EMCCLK_14); also elsewhere on the board
CH4_D23: U1.G16 (IO_L22N_T3_A16_15); also elsewhere on the board
CH4_DE: U1.L13 (IO_L5N_T0_D07_14); also elsewhere on the board
CH4_HPD: U1.R15 (IO_L9P_T1_DQS_14); also elsewhere on the board
CH4_HS: U1.P15 (IO_L8P_T1_D11_14); also elsewhere on the board
CH4_INT: U1.J15 (IO_L23P_T3_FOE_B_15); also elsewhere on the board
CH4_VS: U1.P14 (IO_L12N_T1_MRCC_14); also elsewhere on the board
CLK100: U1.D4 (IO_L12P_T1_MRCC_35); also elsewhere on the board
I2C_A_SCL: U1.H4 (IO_L18N_T2_35); also elsewhere on the board
I2C_A_SDA: U1.H2 (IO_L20P_T3_35); also elsewhere on the board
I2C_B_SCL: U1.E15 (IO_L18N_T2_A23_15); also elsewhere on the board
I2C_B_SDA: U1.E16 (IO_L17P_T2_A26_15); also elsewhere on the board
LED0: U1.R10 (IO_L17P_T2_A14_D30_14); also elsewhere on the board
LED1: U1.R11 (IO_L17N_T2_A13_D29_14); also elsewhere on the board
LED2: U1.T12 (IO_L15N_T2_DQS_DOUT_CSO_B_14); also elsewhere on the board
LED3: U1.R12 (IO_L15P_T2_DQS_RDWR_B_14); also elsewhere on the board
PMOD_1: U1.E5 (IO_L13N_T2_MRCC_35); also elsewhere on the board
PMOD_2: U1.E6 (IO_0_35); also elsewhere on the board
PMOD_3: U1.F5 (IO_L13P_T2_MRCC_35); also elsewhere on the board
PMOD_4: U1.G5 (IO_L16P_T2_35); also elsewhere on the board
PMOD_7: U1.H5 (IO_L18P_T2_35); also elsewhere on the board
PMOD_8: U1.J5 (IO_L19P_T3_35); also elsewhere on the board
PMOD_9: U1.K5 (IO_25_35); also elsewhere on the board
PMOD_10: U1.L5 (IO_0_34); also elsewhere on the board
QSPI_CS: U1.L12 (IO_L6P_T0_FCS_B_14); also elsewhere on the board
QSPI_D0: U1.J13 (IO_L1P_T0_D00_MOSI_14); also elsewhere on the board
QSPI_D1: U1.J14 (IO_L1N_T0_D01_DIN_14); also elsewhere on the board
QSPI_D2: U1.K15 (IO_L2P_T0_D02_14); also elsewhere on the board
QSPI_D3: U1.K16 (IO_L2N_T0_D03_14); also elsewhere on the board
RST_N: U1.T3 (IO_L9N_T1_DQS_34); also elsewhere on the board
SW0: U1.T13 (IO_L16N_T2_A15_D31_14); also elsewhere on the board
SW1: U1.R13 (IO_L16P_T2_CSI_B_14); also elsewhere on the board
SW2: U1.T14 (IO_L10P_T1_D14_14); also elsewhere on the board
SW3: U1.T15 (IO_L10N_T1_D15_14); also elsewhere on the board

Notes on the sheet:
XC7A35T-1FTG256C I/O banks. All banks VCCO = 3.3 V (LVCMOS33). CHn_* nets go to the carrier sockets J1/J2 (see fpga_pinmap.csv).
Assignment is generated by hardware/gen/fpga_common.py: BGA escape plan (ring 1-2 on top, ring 3-4 on In2, deeper on In3) and monotonic
perimeter-order mapping of the 124 header signals so that the fan-out to the sockets does not cross. NC = unused I/O (left open).
